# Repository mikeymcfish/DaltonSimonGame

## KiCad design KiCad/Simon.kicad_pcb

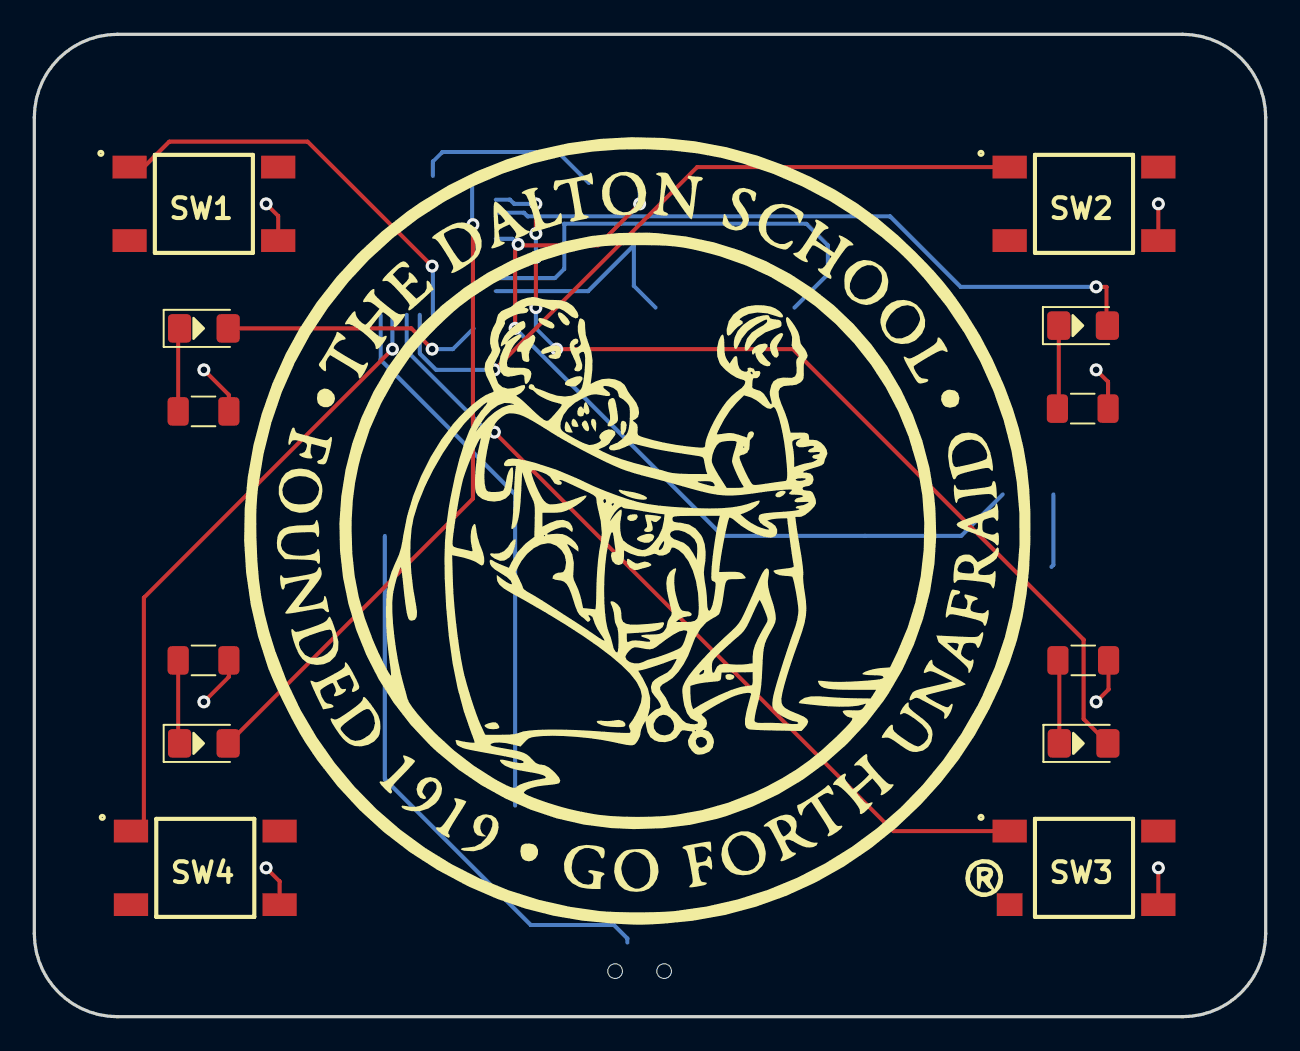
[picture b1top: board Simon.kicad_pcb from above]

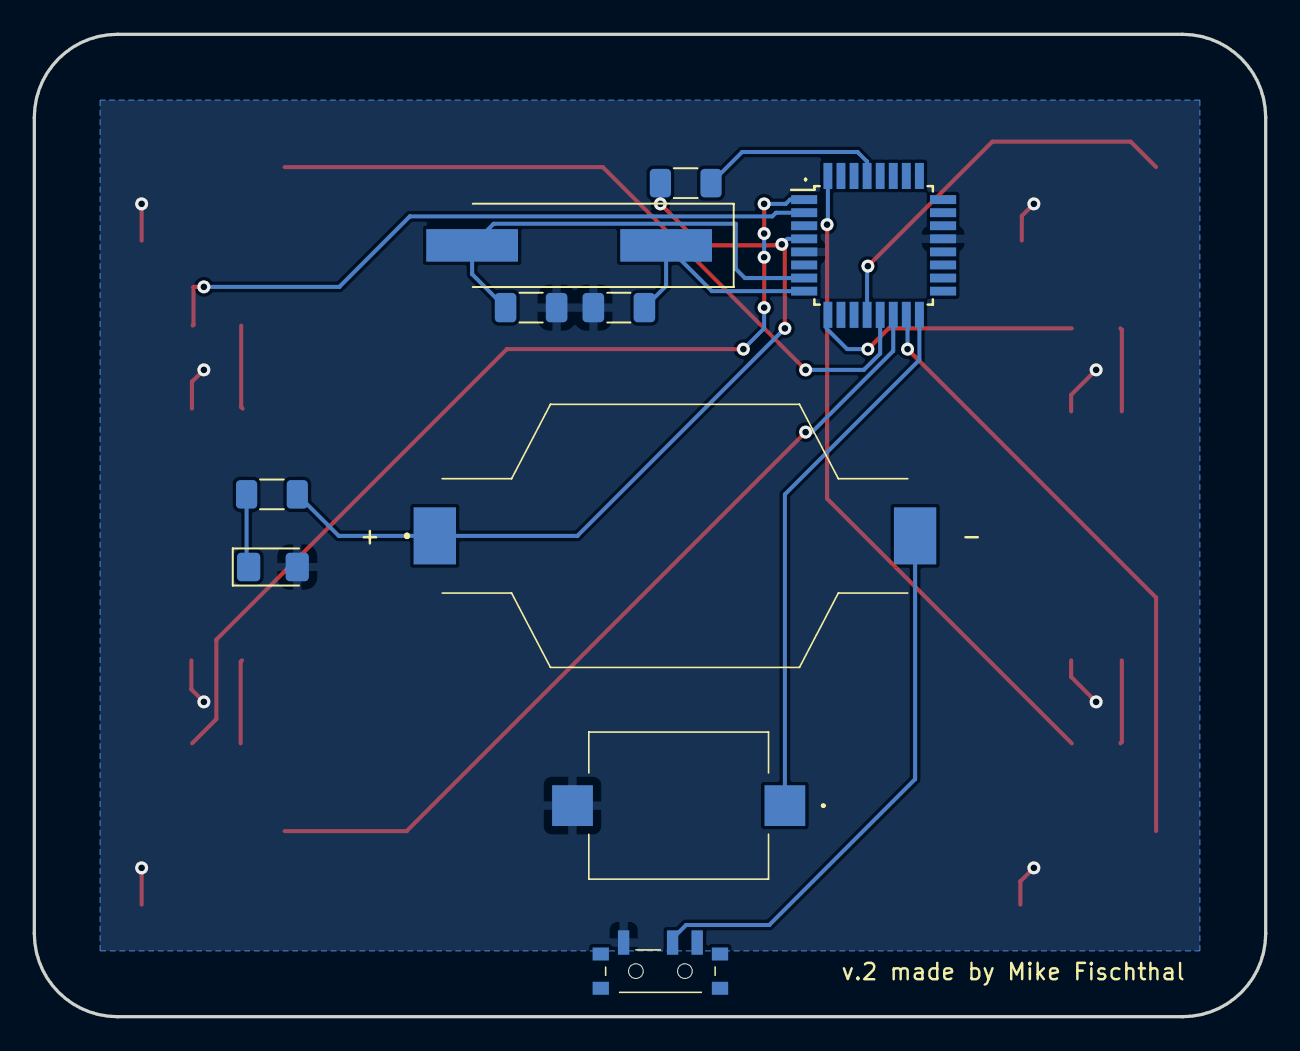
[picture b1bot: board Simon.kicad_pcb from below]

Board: 2 copper layers, 75.4 x 60.1 mm, 22 parts (10 on the bottom side), 20 nets.

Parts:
BT1: 3V; SMTU2032LF
C1, C2: 22pF; C_1206_3216Metric_Pad1.33x1.80mm_HandSolder
D1: BLUE; LED_1206_3216Metric_Pad1.42x1.75mm_HandSolder
D2: GREEN; LED_1206_3216Metric_Pad1.42x1.75mm_HandSolder
D3: YELLOW; LED_1206_3216Metric_Pad1.42x1.75mm_HandSolder
D4, D5: RED; LED_1206_3216Metric_Pad1.42x1.75mm_HandSolder
LS1: Speaker; CPT111783SMTTR
R1: 1kΩ; R_1206_3216Metric_Pad1.30x1.75mm_HandSolder
R2, R3, R4: 330Ω; R_1206_3216Metric_Pad1.30x1.75mm_HandSolder
R5, R6: 470Ω; R_1206_3216Metric_Pad1.30x1.75mm_HandSolder
S1: POWER SW; MSS3VTR
SW1: red; FSM4JSMATR
SW2: green; FSM4JSMATR
SW3: yellow; FSM4JSMATR
SW4: blue; FSM4JSMATR
U1: ATmega328PB-A; TQFP-32_7x7mm_P0.8mm
Y1: 16.00Mhz; Crystal_SMD_HC49-SD_HandSoldering

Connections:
GND: C1.2, C2.2, D5.2 (A), LS1.2, R2.1, R3.2, R4.2, R5.2, S1.A1 (NO), SW1.4 (2), SW2.4 (2), SW3.4 (2), SW4.4 (2), U1.5 (GND), U1.21 (GND)
unnamed: BT1.2 (-), S1.B1 (COM)
unnamed: D1.1 (K), R2.2
unnamed: D1.2 (A), U1.32 (PD2)
unnamed: D2.1 (K), R3.1
unnamed: D2.2 (A), U1.1 (PD3)
unnamed: D3.1 (K), R4.1
unnamed: D3.2 (A), U1.2 (PD4)
unnamed: D4.1 (K), R5.1
unnamed: D4.2 (A), U1.9 (PD5)
unnamed: D5.1 (K), R6.2
unnamed: LS1.1, U1.16 (PB4)
unnamed: R1.2, U1.29 (~RESET/PC6)
unnamed: SW1.1, U1.12 (PB0)
unnamed: SW2.1, U1.13 (PB1)
unnamed: SW3.1, U1.14 (PB2)
unnamed: SW4.1, U1.15 (PB3)
VCC: BT1.1 (+), R1.1, R6.1, U1.4 (VCC)
xtalI: C2.1, U1.7 (XTAL1/PB6), Y1.2
xtalO: C1.1, U1.8 (XTAL2/PB7), Y1.1

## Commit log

2022-04-05 Init
